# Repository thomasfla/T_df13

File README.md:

# T_df13
Simple 2 pin DF13  "T" connector board

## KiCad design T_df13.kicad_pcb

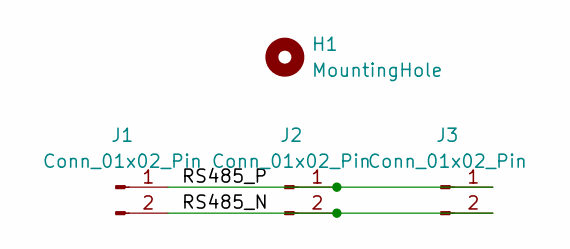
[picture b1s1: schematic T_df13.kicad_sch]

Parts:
H1: MountingHole; MountingHole_2.5mm
J1, J2, J3: Conn_01x02_Pin; Hirose_DF13C_CL535-0402-2-51_1x02-1MP_P1.25mm_Vertical

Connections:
/RS485_N: J1.2, J2.2, J3.2
/RS485_P: J1.1, J2.1, J3.1

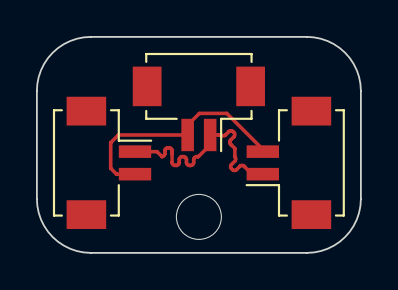
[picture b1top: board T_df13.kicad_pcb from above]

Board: 2 copper layers, 18.0 x 12.0 mm, 4 parts (0 on the bottom side), 2 nets.

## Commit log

2024-02-29 add kicad files
2024-02-29 Update to KiCad8, tune length
